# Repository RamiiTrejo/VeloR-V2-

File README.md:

## VeloR-V2

 Velo será un Robot seguidor de Líneas con una turbina integrada para una mayor agilidad, tambien llevara una regleta de 16 Sensores QRE1113, para una mejor lectura de la pista para lograr competir en la categoria de Carreras Pro de la LNR

<table>
<tr>
<td  colspan="2">  </td>
</tr>
<tr>
<td> 
 </td>
<td> 
 </td>
</tr>
</table>

## 🛠️🧰COMPONENTES
los componentes que utilizara este robot son
- ESP32 embebido
- Motores profast de 3600 RPM
- Ruedas JS2124
- Puentes H TA6586
- Motor Brushless/Coreless como Turbina
- Regleta De 16 [sensores QRE1113](https://github.com/RamiiTrejo/Array-16-Sensors)

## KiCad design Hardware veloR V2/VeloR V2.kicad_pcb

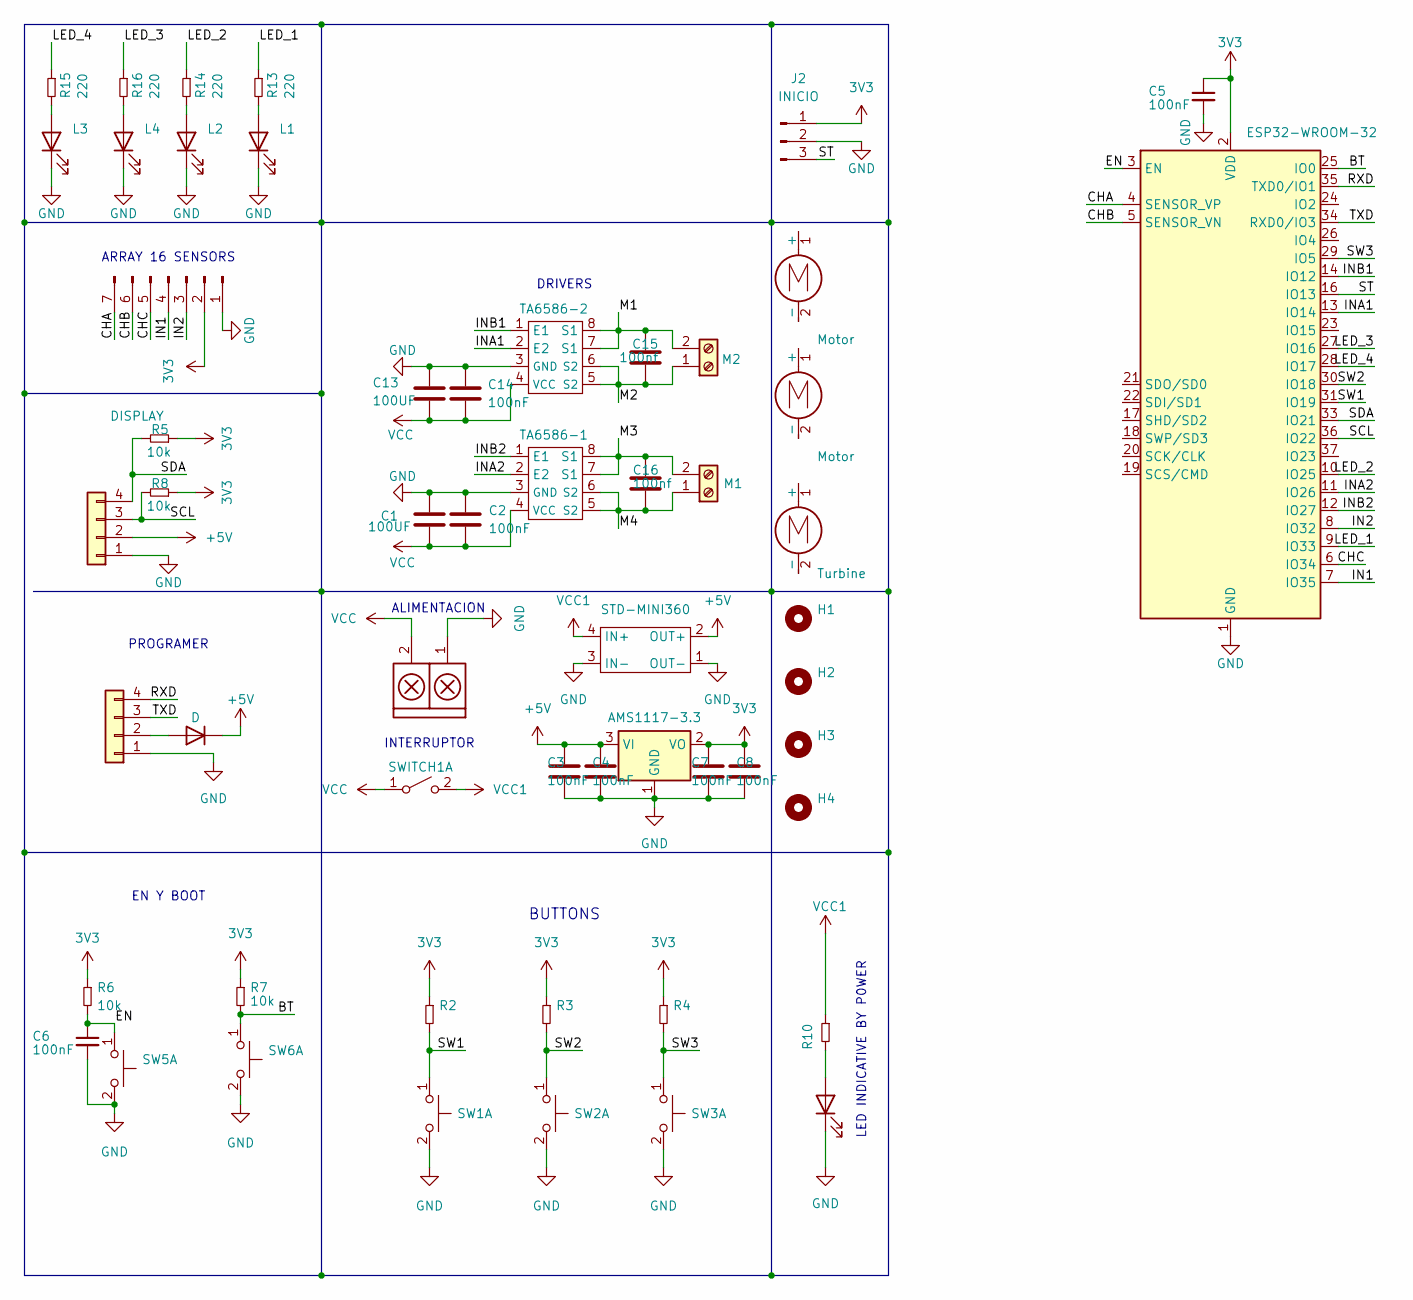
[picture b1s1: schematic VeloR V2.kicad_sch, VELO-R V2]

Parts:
Alimentacion1: TB_1X2; AMASS_XT30U-M_1x02_P5.0mm_Vertical
C1, C13: 100UF; CP_EIA-7343-20_Kemet-V
C2, C3, C4, C5, C6, C7, C8, C14: 100nF; C_0805_2012Metric_Pad1.18x1.45mm_HandSolder
C15, C16: 100nf; C_0805_2012Metric_Pad1.18x1.45mm_HandSolder
D1: D; D_SMA
D2: LED; LED_1206_3216Metric_Pad1.42x1.75mm_HandSolder
H1, H2, H3, H4: MountingHole; MountingHole_3.2mm_M3_DIN965
J1: Conn_01x07_Pin; PinHeader_1x07_P2.54mm_Horizontal
J2: INICIO; PinHeader_1x03_P2.54mm_Vertical
J3: DISPLAY; 128x64OLED
J5: DISPLAY; PinHeader_1x04_P2.54mm_Horizontal
L1, L2, L3, L4: LED; LED_0805_2012Metric_Pad1.15x1.40mm_HandSolder
M1: M1; JST_XH_B2B-XH-A_1x02_P2.50mm_Vertical
M2: M2; JST_XH_B2B-XH-A_1x02_P2.50mm_Vertical
M4, M6: Motor; motor 3600rpm
M5: Turbine; Turbina
R2, R3, R4, R5, R6, R7, R8, R10: 10k; R_0805_2012Metric_Pad1.20x1.40mm_HandSolder
R13, R14, R15, R16: 220; R_0805_2012Metric_Pad1.20x1.40mm_HandSolder
STD-MINI360: STEP DOWN MINI 360
SW1, SW2, SW3, SW5, SW6: SW_Push_Dual_x2; BTN_SMD_3x6x2.5mm
SWITCH1: SW_DPST_x2; PinHeader_1x03_P2.54mm_Vertical
TA6586-1, TA6586-2: DIP-8_W7.62mm
U1: AMS1117-3.3; SOT-223-3_TabPin2
U3: ESP32-WROOM-32

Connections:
3V3: C5.1, C7.1, C8.1, J1.2, J2.1, R2.1, R3.1, R4.1, R5.1, R6.1, R7.1, R8.1, U1.2 (VO), U3.2 (VDD)
+5V: C3.1, C4.1, D1.1 (K), J3.2, STD-MINI360.2 (OUT+), U1.3 (VI)
/BT: R7.2, SW6.1 (C), U3.25 (IO0)
/CHA: J1.7, U3.4 (SENSOR_VP)
/CHB: J1.6, U3.5 (SENSOR_VN)
/CHC: J1.5, U3.6 (IO34)
/EN: C6.1, R6.2, SW5.1 (C), U3.3 (EN)
/IN1: J1.4, U3.7 (IO35)
/IN2: J1.3, U3.8 (IO32)
/INA1: TA6586-2.2 (E2), U3.13 (IO14)
/INA2: TA6586-1.2 (E2), U3.11 (IO26)
/INB1: TA6586-2.1 (E1), U3.14 (IO12)
/INB2: TA6586-1.1 (E1), U3.12 (IO27)
/LED_1: R13.1, U3.9 (IO33)
/LED_2: R14.1, U3.10 (IO25)
/LED_3: R16.1, U3.27 (IO16)
/LED_4: R15.1, U3.28 (IO17)
/M1: C15.1, M2.2, TA6586-2.7 (S1), TA6586-2.8 (S1)
/M2: C15.2, M2.1, TA6586-2.5 (S2), TA6586-2.6 (S2)
/M3: C16.1, M1.2, TA6586-1.7 (S1), TA6586-1.8 (S1)
/M4: C16.2, M1.1, TA6586-1.5 (S2), TA6586-1.6 (S2)
/RXD: J5.4, U3.35 (TXD0/IO1)
/SCL: J3.3, R8.2, U3.36 (IO22)
/SDA: J3.4, R5.2, U3.33 (IO21)
/ST: J2.3, U3.16 (IO13)
/SW1: R2.2, SW1.1 (C), U3.31 (IO19)
/SW2: R3.2, SW2.1 (C), U3.30 (IO18)
/SW3: R4.2, SW3.1 (C), U3.29 (IO5)
/TXD: J5.3, U3.34 (RXD0/IO3)
GND: Alimentacion1.1, C1.1, C2.1, C3.2, C4.2, C5.2, C6.2, C7.2, C8.2, C13.1, C14.1, D2.1 (K), J1.1, J2.2, J3.1, J5.1, L1.1 (K), L2.1 (K), L3.1 (K), L4.1 (K), STD-MINI360.1 (OUT-), STD-MINI360.3 (IN-), SW1.2 (D), SW2.2 (D), SW3.2 (D), SW5.2 (D), SW6.2 (D), TA6586-1.3 (GND), TA6586-2.3 (GND), U1.1 (GND), U3.1 (GND), U3.15 (GND), U3.38 (GND), U3.39 (GND)
unnamed: D1.2 (A), J5.2
unnamed: D2.2 (A), R10.2
unnamed: L1.2 (A), R13.2
unnamed: L2.2 (A), R14.2
unnamed: L3.2 (A), R15.2
unnamed: L4.2 (A), R16.2
VCC: Alimentacion1.2, C1.2, C2.2, C13.2, C14.2, SWITCH1.1 (A), TA6586-1.4 (VCC), TA6586-2.4 (VCC)
VCC1: R10.1, STD-MINI360.4 (IN+), SWITCH1.2 (B)

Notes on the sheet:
ALIMENTACION
INTERRUPTOR
BUTTONS
LED INDICATIVE BY P0WER
DRIVERS
ARRAY 16 SENSORS
EN Y BOOT
PROGRAMER

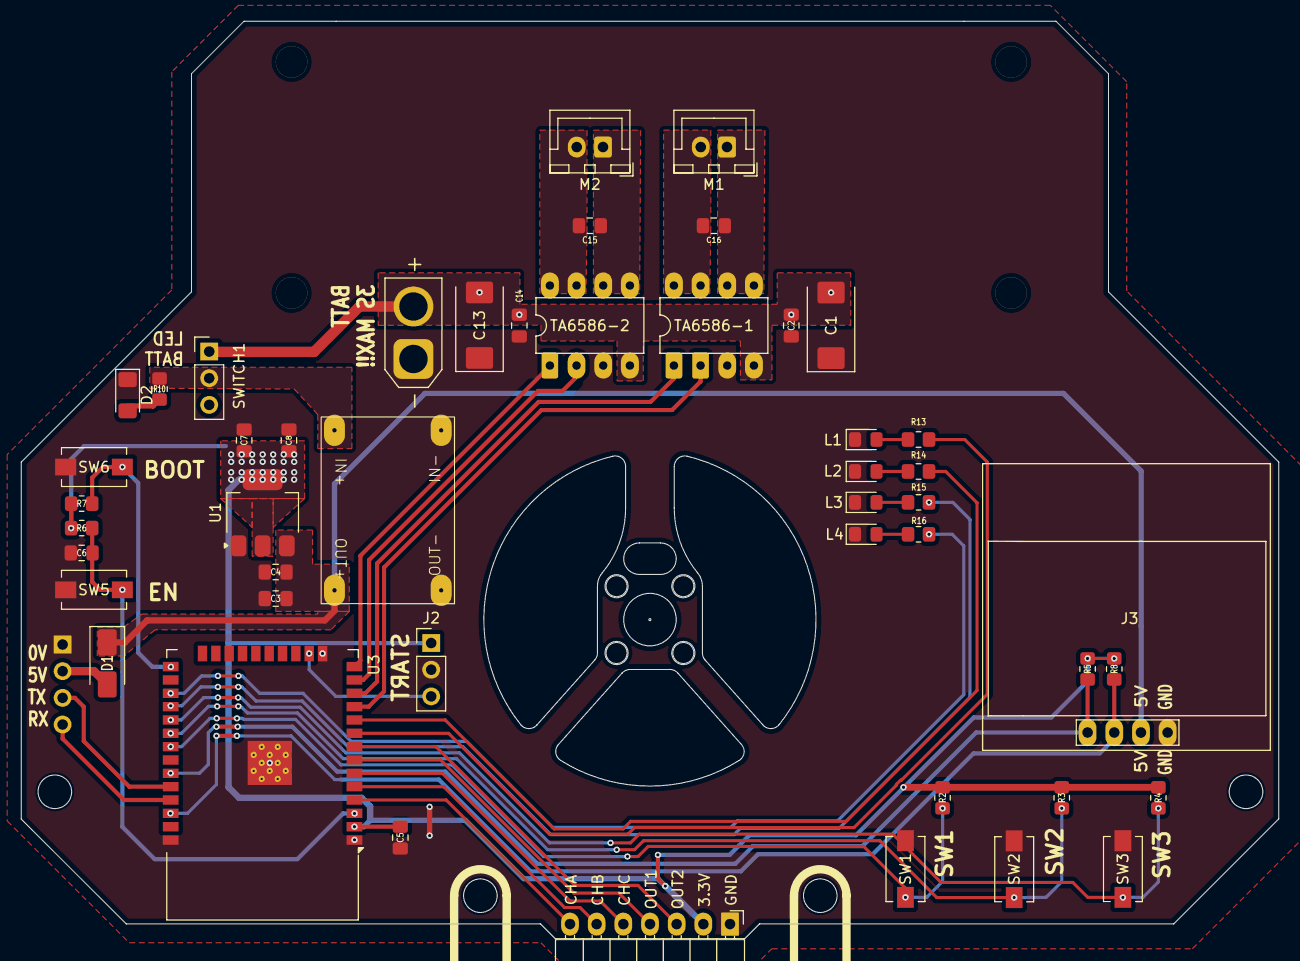
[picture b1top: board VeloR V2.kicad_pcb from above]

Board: 2 copper layers, 119.7 x 87.4 mm, 57 parts (1 on the bottom side), 38 nets.

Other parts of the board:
H3#2, H4#2: MountingHole; MountingHole_3.2mm_M3_DIN965

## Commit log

2026-01-05 Add files via upload
    Archivo de Kicad de veloR, con sus detalles de silkscreeen , etc
